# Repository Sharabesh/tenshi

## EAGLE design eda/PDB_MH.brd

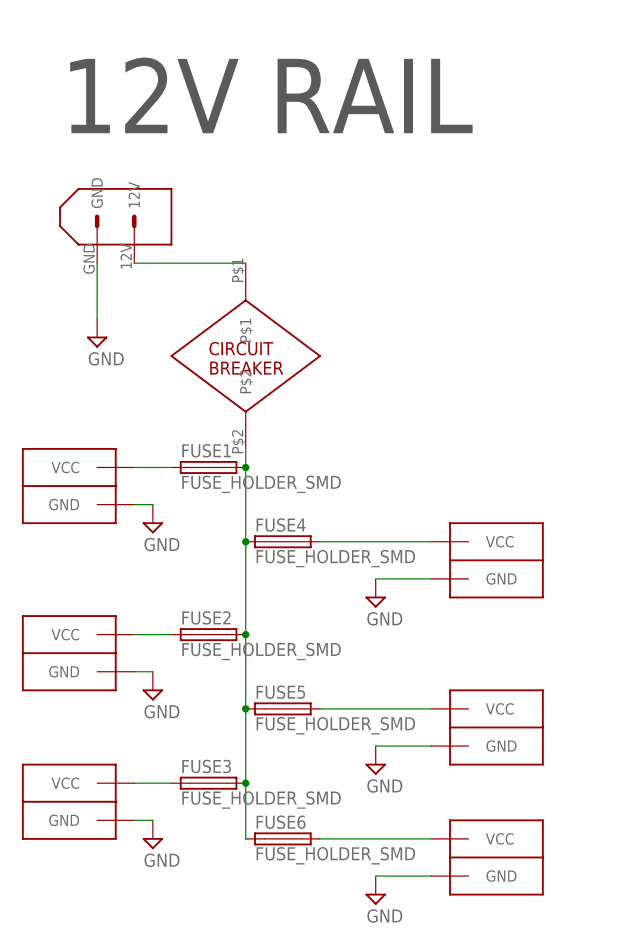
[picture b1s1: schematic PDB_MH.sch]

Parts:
CIRCUIT_BREAKER: CIRC_BREAKER
CONN1, CONN2, CONN3, CONN4, CONN5, CONN6: ANDERSONVERTICAL; ANDERSON_VERTICAL
FUSE1, FUSE2, FUSE3, FUSE4, FUSE5, FUSE6: FUSE_HOLDER_SMD
U$1: XT60CONNECTOR

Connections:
12V: CIRCUIT_BREAKER.P$2, FUSE1.P$2_DOWN (2), FUSE1.P$2_UP (2), FUSE2.P$2_DOWN (2), FUSE2.P$2_UP (2), FUSE3.P$2_DOWN (2), FUSE3.P$2_UP (2), FUSE4.P$1_DOWN (1), FUSE4.P$1_UP (1), FUSE5.P$1_DOWN (1), FUSE5.P$1_UP (1), FUSE6.P$1_DOWN (1), FUSE6.P$1_UP (1)
BAT: CIRCUIT_BREAKER.P$1, U$1.12V
GND: CONN1.PIN1 (GND), CONN2.PIN1 (GND), CONN3.PIN1 (GND), CONN4.PIN1 (GND), CONN5.PIN1 (GND), CONN6.PIN1 (GND), U$1.GND
VOUT1: CONN1.PIN2 (VCC), FUSE1.P$1_DOWN (1), FUSE1.P$1_UP (1)
VOUT2: CONN2.PIN2 (VCC), FUSE2.P$1_DOWN (1), FUSE2.P$1_UP (1)
VOUT3: CONN3.PIN2 (VCC), FUSE3.P$1_DOWN (1), FUSE3.P$1_UP (1)
VOUT4: CONN4.PIN2 (VCC), FUSE4.P$2_DOWN (2), FUSE4.P$2_UP (2)
VOUT5: CONN5.PIN2 (VCC), FUSE5.P$2_DOWN (2), FUSE5.P$2_UP (2)
VOUT6: CONN6.PIN2 (VCC), FUSE6.P$2_DOWN (2), FUSE6.P$2_UP (2)

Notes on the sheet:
12V RAIL

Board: 2 copper layers, 19 parts (1 on the bottom side), 9 nets, no tracks yet.

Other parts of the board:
U$2, U$3, U$4, U$5: STAND-OFF
U$6: PIE-LOGO-SMALL

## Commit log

2016-08-27 Incorporated Mohammad's Part into Pie Library

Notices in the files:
eda/PDB_MH.brd:
Copyright (c) 2013, Pioneers in Engineering
All rights reserved.
